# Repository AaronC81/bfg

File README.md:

# The BFG - Basic Function Generator

The BFG is a small, minimalistic function generator based around the
[AD9833](https://www.analog.com/media/en/technical-documentation/data-sheets/AD9833.pdf),
controlled by an ATmega328P with a lovely little OLED display and rotary
encoder.

- Sine, square and triangle waves
- Powered over Micro USB
- Output range of 0 to 5 volts
- Theoretical maximum output frequency of 12.5MHz

At high frequencies (>2MHz) the range of voltages begins to narrow; for example,
a sine wave at 5MHz set to an amplitude of 5V only actually oscillates between
about 1.5V and 4V. These frequencies are a tad much for my poor USB oscilloscope
to handle, so I can't accurately measure the practical limits.

I built this for two main reasons:

- To have a basic function generator for embedded projects
- To learn simple surface-mount soldering

# How it Works

As the rather lovely silkscreen on the board suggests, functions are generated
by three steps:

1. **Generate**: The AD9833 generates a low-voltage signal, about 0.65V
2. **Amplify**: The AD8052 op-amp amplifies the signal to 5V
3. **Scale**: The MCP4131 digital potentiometer divides the signal down to the desired amplitude

# Repo

`cad` contains KiCad files for the PCB.

`firmware` contains a platform.io project for the ATmega328P's firmware.

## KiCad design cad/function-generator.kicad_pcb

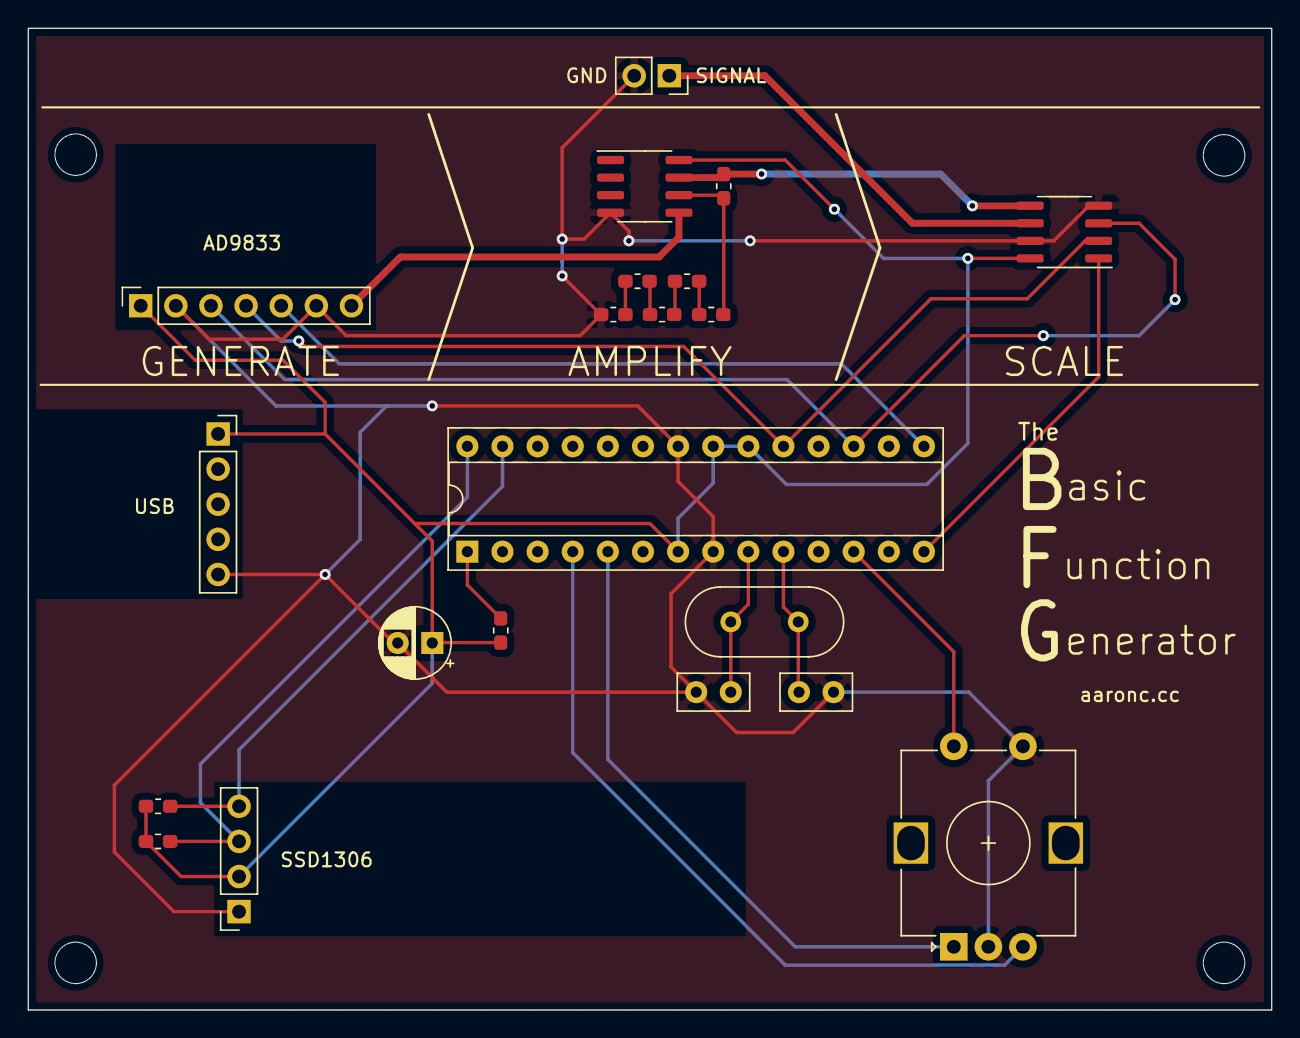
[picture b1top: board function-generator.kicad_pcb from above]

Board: 2 copper layers, 89.9 x 71.0 mm, 21 parts (0 on the bottom side), 22 nets.

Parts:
C1: 10uF; CP_Radial_D5.0mm_P2.50mm
C2, C3: 22pF; C_Disc_D5.0mm_W2.5mm_P2.50mm
J1: USB_B_Micro_NoShield; PinSocket_1x05_P2.54mm_Vertical
J2: Conn_01x02_Female; PinSocket_1x02_P2.54mm_Vertical
R1, R2, R3, R12: 4.7k; R_0603_1608Metric_Pad1.05x0.95mm_HandSolder
R7: 680; R_0603_1608Metric_Pad1.05x0.95mm_HandSolder
R8: 10; R_0603_1608Metric_Pad1.05x0.95mm_HandSolder
R9, R10, R11: 4.7; R_0603_1608Metric_Pad1.05x0.95mm_HandSolder
SW1: Rotary_Encoder_Switch; RotaryEncoder_Alps_EC12E-Switch_Vertical_H20mm
U1: ATmega328P-PU; DIP-28_W7.62mm_Socket
U2: SSD1306_128x32; PinSocket_1x04_P2.54mm_Vertical
U3: MCP4131; SOIC-8_3.9x4.9mm_P1.27mm
U4: AD9833_Breakout; PinSocket_1x07_P2.54mm_Vertical
U5: AD8052; SOIC-8_3.9x4.9mm_P1.27mm
Y1: 16MHz; Crystal_HC49-4H_Vertical

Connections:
5VSIG: R12.1, U3.5, U5.7
FGCS: U1.15, U4.5
GND: C1.2, C2.2, C3.2, J1.5, J2.2, R11.2, SW1.C, SW1.S2, U1.8, U1.22, U2.1, U3.4, U3.7, U4.2, U4.6, U5.4
MOSI: U1.17, U3.3, U4.3
unnamed: R3.2, U1.1
unnamed: R7.2, R8.1
unnamed: R8.2, R9.1
unnamed: R9.2, R10.1
unnamed: R10.2, R11.1
unnamed: R7.1, R12.2, U5.6
POTCS: U1.14, U3.1
ROTCLK: SW1.A, U1.5
ROTDT: SW1.B, U1.4
ROTSW: SW1.S1, U1.12
SCK: U1.19, U3.2, U4.4
SCL: R2.2, U1.28, U2.3
SDA: R1.2, U1.27, U2.4
SIG: J2.1, U3.6
VCC: C1.1, J1.1, R1.1, R2.1, R3.1, U1.7, U1.20, U1.21, U2.2, U3.8, U4.1, U5.8
WEAKSIG: U4.7, U5.5
XTAL1: C2.1, U1.9, Y1.1
XTAL2: C3.1, U1.10, Y1.2

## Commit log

2020-08-26 Not entirely sure what this changed but sure
2020-08-26 Fill out README
